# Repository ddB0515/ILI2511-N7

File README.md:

# ILI2511-N7

Nexus 7(2nd gen) touch controller board based on Ilitek 2511 (only USB and I2C is supported)

# Interactive BOM
[Interactive BOM](http://htmlpreview.github.io/?https://raw.githubusercontent.com/ddB0515/ILI2511-N7/master/hardware/bom/ibom.html)

## LOG
* v1 inital version
* v2 updated FPC connector (got it working)
* v3 updated footprint to get easier solder and visual check 

## Revisions

 * v1 is currently in testing stage (waiting board to arrive so can test it)
 will update progress here later on
 * v2 working prototype (need slight biggger foorptint for ILI2511)
 * v3 updated footprint and new routing 

## Licence

 * Hardware in this repository is licenced under CERN OHL v1.2

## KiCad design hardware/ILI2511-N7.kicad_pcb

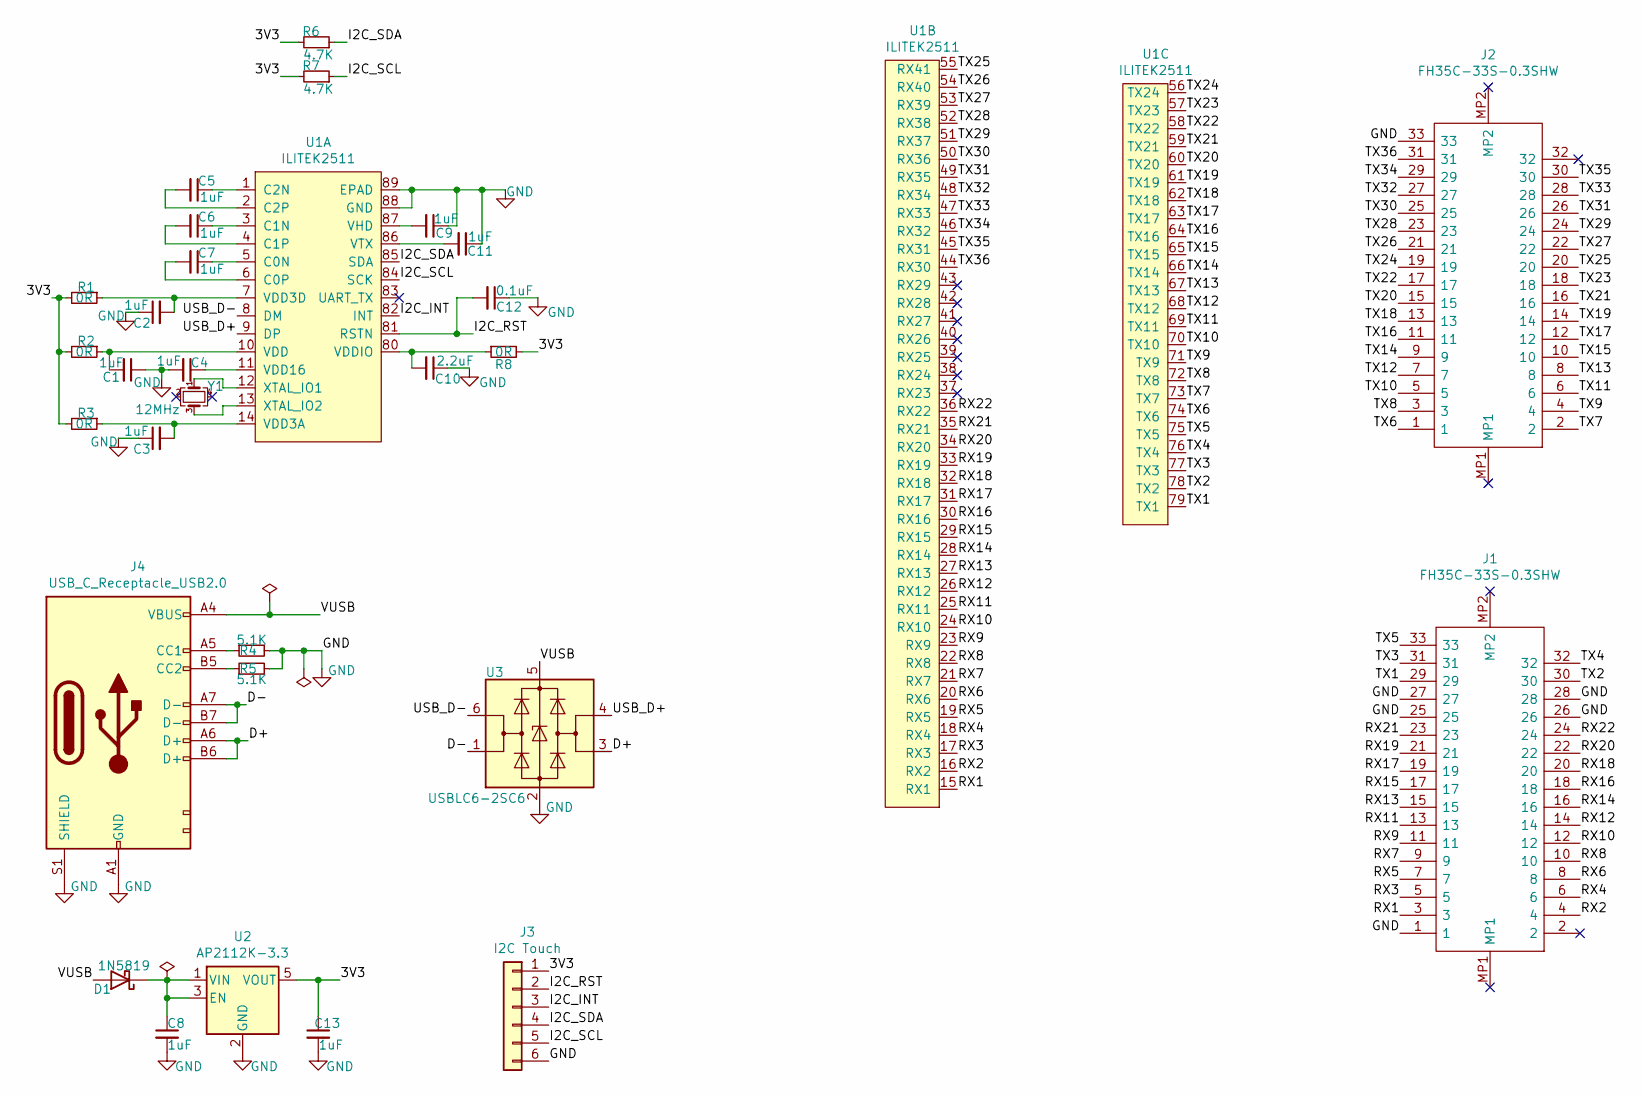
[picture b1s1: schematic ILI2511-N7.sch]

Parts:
C1, C2, C3, C4, C5, C6, C7, C8, C9, C11, C13: 1uF; C_0402_1005Metric
C10: 2.2uF; C_0402_1005Metric
C12: 0.1uF; C_0402_1005Metric
D1: 1N5819; D_SOD-123
J1, J2: FH35C-33S-0.3SHW; FH35C33S03SHW; Mouser Part Number 798-FH35C33S03SHW99
J3: I2C Touch; PinHeader_1x06_P2.54mm_Vertical
J4: USB_C_Receptacle_USB2.0; USB-C_C168688
R1, R2, R3, R8: 0R; R_0603_1608Metric
R4, R5: 5.1K; R_0603_1608Metric
R6, R7: 4.7K; R_0603_1608Metric
U1: ILITEK2511; ILITEK-2511
U2: AP2112K-3.3; SOT-23-5
U3: USBLC6-2SC6; SOT-23-6
Y1: 12MHz; Oscillator_SMD_ECS_2520MV-xxx-xx-4Pin_2.5x2.0mm

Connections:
/3V3: C13.1, J3.1, R1.2, R2.2, R3.2, R6.2, R7.2, R8.2, U2.5 (VOUT)
/D+: J4.A6 (D+), J4.B6 (D+), U3.3 (I/O2)
/D-: J4.A7 (D-), J4.B7 (D-), U3.1 (I/O1)
/I2C_INT: J3.3, U1.82 (INT)
/I2C_RST: C12.2, J3.2, U1.81 (RSTN)
/I2C_SCL: J3.5, R7.1, U1.84 (SCK)
/I2C_SDA: J3.4, R6.1, U1.85 (SDA)
/RX1: J1.3, U1.15 (RX1)
/RX2: J1.4, U1.16 (RX2)
/RX3: J1.5, U1.17 (RX3)
/RX4: J1.6, U1.18 (RX4)
/RX5: J1.7, U1.19 (RX5)
/RX6: J1.8, U1.20 (RX6)
/RX7: J1.9, U1.21 (RX7)
/RX8: J1.10, U1.22 (RX8)
/RX9: J1.11, U1.23 (RX9)
/RX10: J1.12, U1.24 (RX10)
/RX11: J1.13, U1.25 (RX11)
/RX12: J1.14, U1.26 (RX12)
/RX13: J1.15, U1.27 (RX13)
/RX14: J1.16, U1.28 (RX14)
/RX15: J1.17, U1.29 (RX15)
/RX16: J1.18, U1.30 (RX16)
/RX17: J1.19, U1.31 (RX17)
/RX18: J1.20, U1.32 (RX18)
/RX19: J1.21, U1.33 (RX19)
/RX20: J1.22, U1.34 (RX20)
/RX21: J1.23, U1.35 (RX21)
/RX22: J1.24, U1.36 (RX22)
/TX1: J1.29, U1.79 (TX1)
/TX2: J1.30, U1.78 (TX2)
/TX3: J1.31, U1.77 (TX3)
/TX4: J1.32, U1.76 (TX4)
/TX5: J1.33, U1.75 (TX5)
/TX6: J2.1, U1.74 (TX6)
/TX7: J2.2, U1.73 (TX7)
/TX8: J2.3, U1.72 (TX8)
/TX9: J2.4, U1.71 (TX9)
/TX10: J2.5, U1.70 (TX10)
/TX11: J2.6, U1.69 (TX11)
/TX12: J2.7, U1.68 (TX12)
/TX13: J2.8, U1.67 (TX13)
/TX14: J2.9, U1.66 (TX14)
/TX15: J2.10, U1.65 (TX15)
/TX16: J2.11, U1.64 (TX16)
/TX17: J2.12, U1.63 (TX17)
/TX18: J2.13, U1.62 (TX18)
/TX19: J2.14, U1.61 (TX19)
/TX20: J2.15, U1.60 (TX20)
/TX21: J2.16, U1.59 (TX21)
/TX22: J2.17, U1.58 (TX22)
/TX23: J2.18, U1.57 (TX23)
/TX24: J2.19, U1.56 (TX24)
/TX25: J2.20, U1.55 (RX41)
/TX26: J2.21, U1.54 (RX40)
/TX27: J2.22, U1.53 (RX39)
/TX28: J2.23, U1.52 (RX38)
/TX29: J2.24, U1.51 (RX37)
/TX30: J2.25, U1.50 (RX36)
/TX31: J2.26, U1.49 (RX35)
/TX32: J2.27, U1.48 (RX34)
/TX33: J2.28, U1.47 (RX33)
/TX34: J2.29, U1.46 (RX32)
/TX35: J2.30, U1.45 (RX31)
/TX36: J2.31, U1.44 (RX30)
/USB_D+: U1.9 (DP), U3.4 (I/O2)
/USB_D-: U1.8 (DM), U3.6 (I/O1)
/VUSB: D1.2 (A), J4.A4 (VBUS), U3.5 (VBUS)
GND: C1.1, C2.1, C3.1, C4.2, C8.2, C9.1, C10.1, C11.1, C12.1, C13.2, J1.1, J1.25, J1.26, J1.27, J1.28, J2.33, J3.6, J4.A1 (GND), J4.S1 (SHIELD), R4.2, R5.2, U1.88 (GND), U1.89 (EPAD), U2.2 (GND), U3.2 (GND)
unnamed: C1.2, R2.1, U1.10 (VDD)
unnamed: C2.2, R1.1, U1.7 (VDD3D)
unnamed: C3.2, R3.1, U1.14 (VDD3A)
unnamed: C4.1, U1.11 (VDD16)
unnamed: C5.1, U1.1 (C2N)
unnamed: C5.2, U1.2 (C2P)
unnamed: C6.1, U1.3 (C1N)
unnamed: C6.2, U1.4 (C1P)
unnamed: C7.1, U1.5 (C0N)
unnamed: C7.2, U1.6 (C0P)
unnamed: C8.1, D1.1 (K), U2.1 (VIN), U2.3 (EN)
unnamed: C9.2, U1.87 (VHD)
unnamed: C10.2, R8.1, U1.80 (VDDIO)
unnamed: C11.2, U1.86 (VTX)
unnamed: J4.A5 (CC1), R4.1
unnamed: J4.B5 (CC2), R5.1
unnamed: U1.12 (XTAL_IO1), Y1.1
unnamed: U1.13 (XTAL_IO2), Y1.3

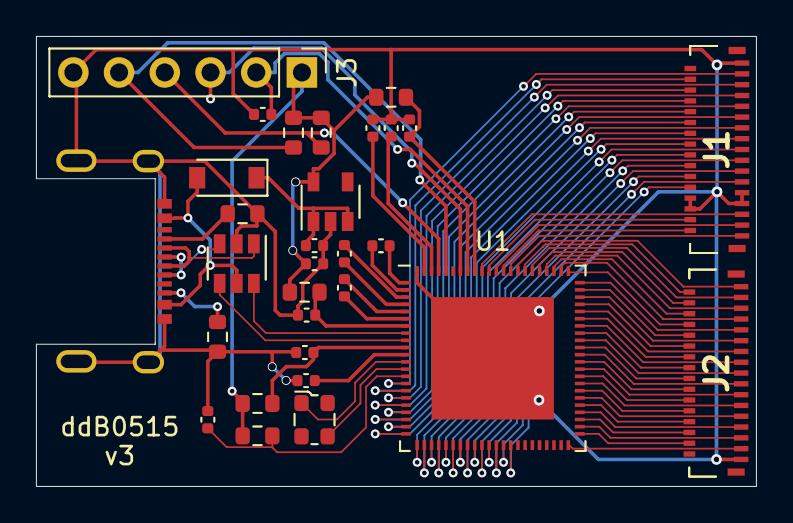
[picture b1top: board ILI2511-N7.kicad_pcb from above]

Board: 2 copper layers, 40.0 x 25.0 mm, 30 parts (0 on the bottom side), 87 nets.

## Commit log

2020-11-13 initial push, finished v1
2020-11-16 added Interactive BOM
2020-11-21 added v2 with Hirose connector (as Molex was not good choice)
2020-11-21 deleted schematic(moved to hardware folder)
2020-12-09 updated PCB footprint and new routing
2020-12-09 updated to v3
